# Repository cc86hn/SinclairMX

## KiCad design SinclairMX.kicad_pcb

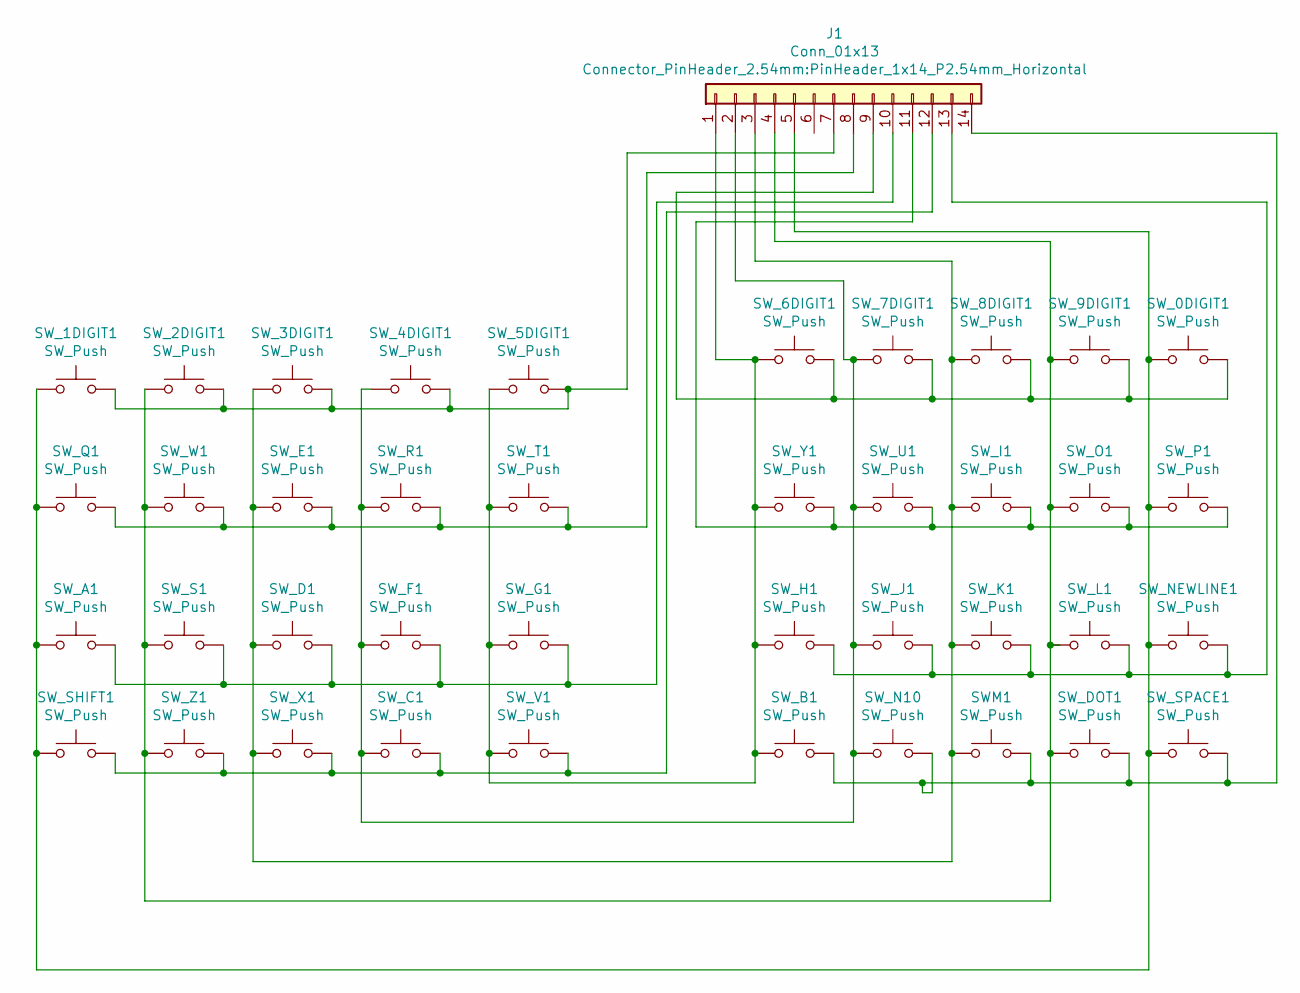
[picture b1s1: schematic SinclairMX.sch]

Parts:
J1: Conn_01x13; PinHeader_1x14_P2.54mm_Horizontal
SWM1: SW_Push; SW_Cherry_MX_1.00u_PCB
SW_0DIGIT1, SW_1DIGIT1, SW_2DIGIT1, SW_3DIGIT1, SW_4DIGIT1, SW_5DIGIT1, SW_6DIGIT1, SW_7DIGIT1, SW_8DIGIT1, SW_9DIGIT1: SW_Push; SW_Cherry_MX_1.00u_PCB
SW_A1: SW_Push; SW_Cherry_MX_1.00u_PCB
SW_B1: SW_Push; SW_Cherry_MX_1.00u_PCB
SW_C1: SW_Push; SW_Cherry_MX_1.00u_PCB
SW_D1: SW_Push; SW_Cherry_MX_1.00u_PCB
SW_DOT1: SW_Push; SW_Cherry_MX_1.00u_PCB
SW_E1: SW_Push; SW_Cherry_MX_1.00u_PCB
SW_F1: SW_Push; SW_Cherry_MX_1.00u_PCB
SW_G1: SW_Push; SW_Cherry_MX_1.00u_PCB
SW_H1: SW_Push; SW_Cherry_MX_1.00u_PCB
SW_I1: SW_Push; SW_Cherry_MX_1.00u_PCB
SW_J1: SW_Push; SW_Cherry_MX_1.00u_PCB
SW_K1: SW_Push; SW_Cherry_MX_1.00u_PCB
SW_L1: SW_Push; SW_Cherry_MX_1.00u_PCB
SW_N10: SW_Push; SW_Cherry_MX_1.00u_PCB
SW_NEWLINE1: SW_Push; SW_Cherry_MX_1.00u_PCB
SW_O1: SW_Push; SW_Cherry_MX_1.00u_PCB
SW_P1: SW_Push; SW_Cherry_MX_1.00u_PCB
SW_Q1: SW_Push; SW_Cherry_MX_1.00u_PCB
SW_R1: SW_Push; SW_Cherry_MX_1.00u_PCB
SW_S1: SW_Push; SW_Cherry_MX_1.00u_PCB
SW_SHIFT1: SW_Push; SW_Cherry_MX_1.00u_PCB
SW_SPACE1: SW_Push; SW_Cherry_MX_1.00u_PCB
SW_T1: SW_Push; SW_Cherry_MX_1.00u_PCB
SW_U1: SW_Push; SW_Cherry_MX_1.00u_PCB
SW_V1: SW_Push; SW_Cherry_MX_1.00u_PCB
SW_W1: SW_Push; SW_Cherry_MX_1.00u_PCB
SW_X1: SW_Push; SW_Cherry_MX_1.00u_PCB
SW_Y1: SW_Push; SW_Cherry_MX_1.00u_PCB
SW_Z1: SW_Push; SW_Cherry_MX_1.00u_PCB

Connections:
unnamed: J1.1, SW_5DIGIT1.1, SW_6DIGIT1.1, SW_B1.1, SW_G1.1, SW_H1.1, SW_T1.1, SW_V1.1, SW_Y1.1
unnamed: J1.2, SW_4DIGIT1.1, SW_7DIGIT1.1, SW_C1.1, SW_F1.1, SW_J1.1, SW_N10.1, SW_R1.1, SW_U1.1
unnamed: J1.3, SWM1.1, SW_3DIGIT1.1, SW_8DIGIT1.1, SW_D1.1, SW_E1.1, SW_I1.1, SW_K1.1, SW_X1.1
unnamed: J1.4, SW_2DIGIT1.1, SW_9DIGIT1.1, SW_DOT1.1, SW_L1.1, SW_O1.1, SW_S1.1, SW_W1.1, SW_Z1.1
unnamed: J1.5, SW_0DIGIT1.1, SW_1DIGIT1.1, SW_A1.1, SW_NEWLINE1.1, SW_P1.1, SW_Q1.1, SW_SHIFT1.1, SW_SPACE1.1
unnamed: J1.7, SW_1DIGIT1.2, SW_2DIGIT1.2, SW_3DIGIT1.2, SW_4DIGIT1.2, SW_5DIGIT1.2
unnamed: J1.8, SW_E1.2, SW_Q1.2, SW_R1.2, SW_T1.2, SW_W1.2
unnamed: J1.9, SW_0DIGIT1.2, SW_6DIGIT1.2, SW_7DIGIT1.2, SW_8DIGIT1.2, SW_9DIGIT1.2
unnamed: J1.10, SW_A1.2, SW_D1.2, SW_F1.2, SW_G1.2, SW_S1.2
unnamed: J1.11, SW_I1.2, SW_O1.2, SW_P1.2, SW_U1.2, SW_Y1.2
unnamed: J1.12, SW_C1.2, SW_SHIFT1.2, SW_V1.2, SW_X1.2, SW_Z1.2
unnamed: J1.13, SW_H1.2, SW_J1.2, SW_K1.2, SW_L1.2, SW_NEWLINE1.2
unnamed: J1.14, SWM1.2, SW_B1.2, SW_DOT1.2, SW_N10.2, SW_SPACE1.2

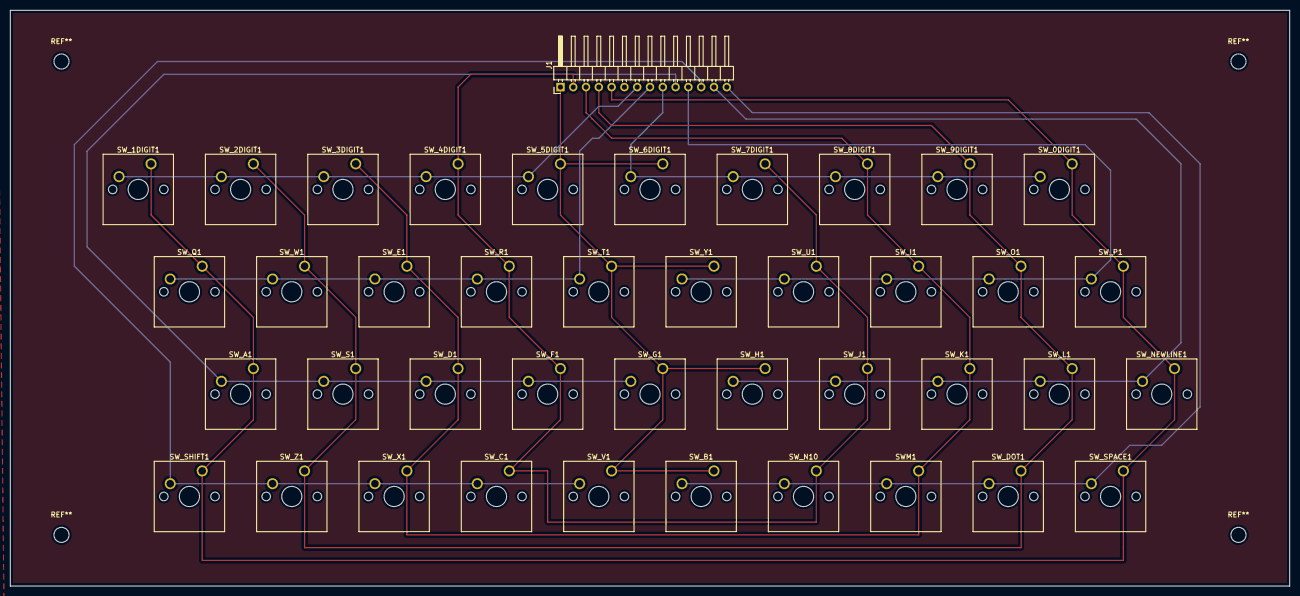
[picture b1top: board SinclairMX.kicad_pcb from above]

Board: 2 copper layers, 254.0 x 114.3 mm, 41 parts (0 on the bottom side), 13 nets.

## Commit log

2019-12-19 initial
